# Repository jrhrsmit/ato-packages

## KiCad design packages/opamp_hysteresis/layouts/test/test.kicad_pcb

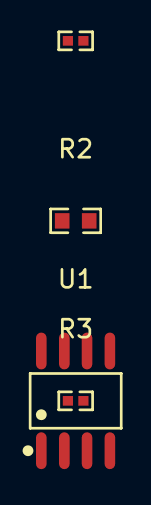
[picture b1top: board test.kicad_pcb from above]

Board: 2 copper layers, 4 parts (0 on the bottom side), 4 nets, no tracks yet.

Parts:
R1, R3: 50kΩ ±1% 62.5mW; R0402
R2: 100kΩ ±1% 100mW; R0603
U1: BW CMRR Ib Vos GBW Iout SR; SOIC-8_L4.9-W3.9-P1.27-LS6.0-BL

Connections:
gnd: R3.2, U1.4
hv: R2.1, U1.8
non_inverting_input: R1.1, R2.2, R3.1, U1.3
output: R1.2, U1.1

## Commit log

2025-06-11 Remove Ruben stuff
2025-06-11 Add OpampMulti and OpampHysteresis
2025-06-12 opamp: improve calc, still needs fix
